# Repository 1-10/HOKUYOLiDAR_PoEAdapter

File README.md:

# HOKUYO LiDAR PoEAdapter

## はじめに

 HOKUYO LiDAR(USTシリーズ)のPoE化に関する資料です。
 
## フォルダ構成
| フォルダ名 | 内容 |
|:---------|:-----|
| App | 動作確認用App Installer |
| Eagle | Eagle回路図 |
| Pic | 画像 |
| stl | 基板ケースSTL |

## 動作確認用App
動作確認用Appは以下を利用しています。WindowsOSのみ対応。
* [URG Benri Lite](https://urgbenri.sourceforge.net/jp/)
## ドキュメント
* [1-10LabBlog](Link)
  * 基板発注先によってデザインルールが異なるため、ガーバーデータは含まれていません。
  * 3Dプリンタ機器によってデータ拡張子が異なるため、STLデータのみになります。

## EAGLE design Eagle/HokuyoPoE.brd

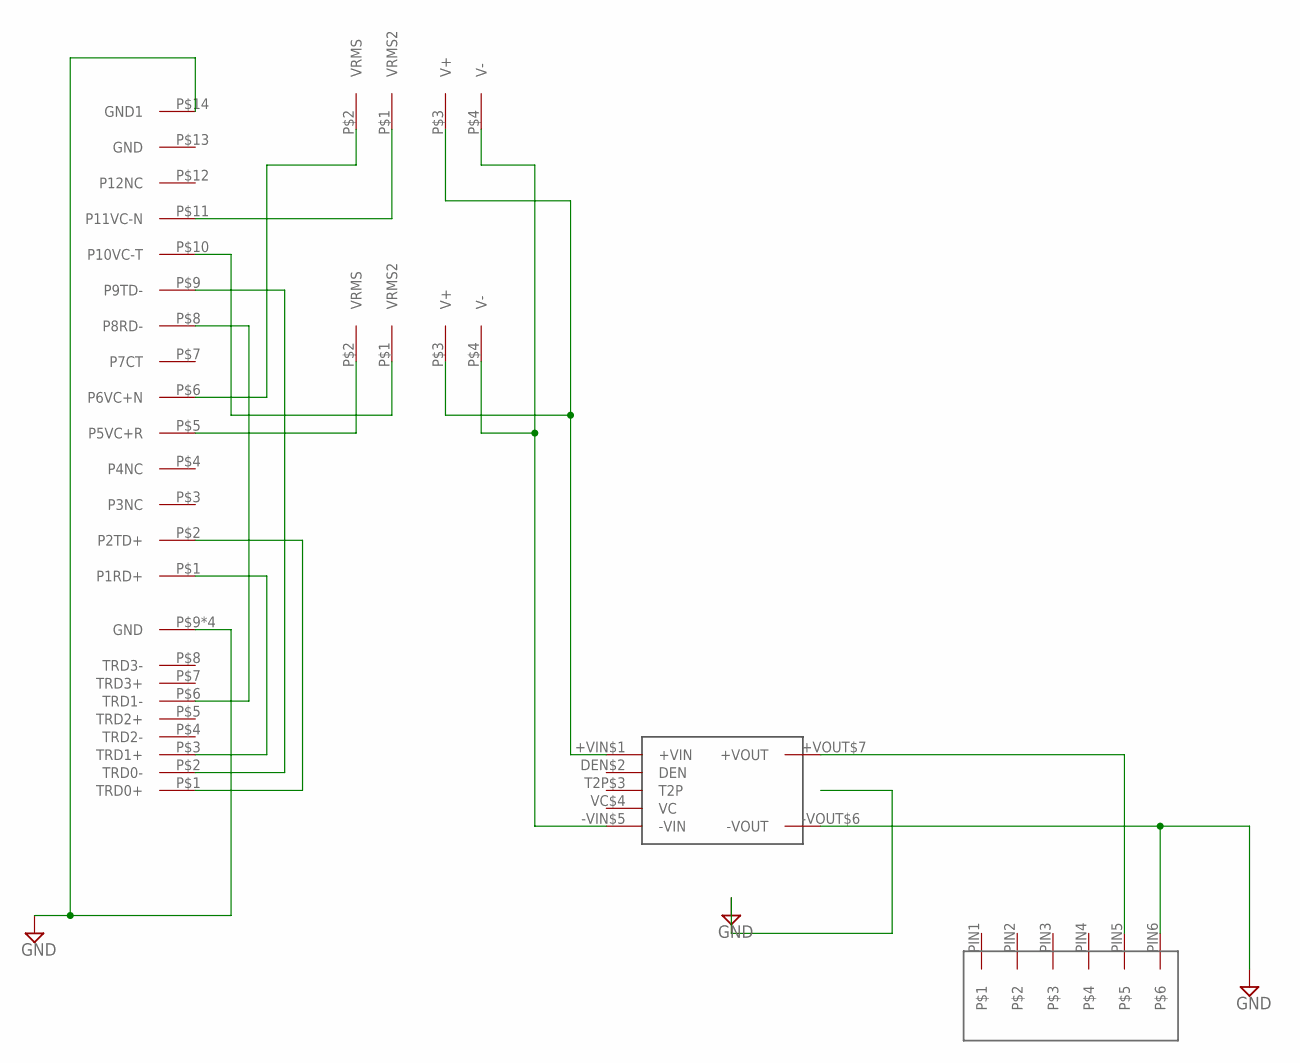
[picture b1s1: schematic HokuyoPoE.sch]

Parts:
U$1: MYBSP0122BABFT
U$2: 7810-XPXC[RJ45]
U$3, U$6: B1010S
U$4: SM08B-SRSS-TB
U$5: 0813-1X1T-57-F

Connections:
GND: U$1.-VOUT$6 (-VOUT), U$2.P$9 (GND), U$2.P$10 (GND), U$2.P$11 (GND), U$2.P$12 (GND), U$4.PIN6, U$5.P$14 (GND1)
unnamed: U$2.P$3 (TRD1+), U$5.P$1 (P1RD+)
unnamed: U$5.P$10 (P10VC-T), U$6.P$1 (VRMS2)
unnamed: U$5.P$5 (P5VC+R), U$6.P$2 (VRMS)
unnamed: U$3.P$1 (VRMS2), U$5.P$11 (P11VC-N)
unnamed: U$3.P$2 (VRMS), U$5.P$6 (P6VC+N)
unnamed: U$1.+VIN$1 (+VIN), U$3.P$3 (V+), U$6.P$3 (V+)
unnamed: U$2.P$6 (TRD1-), U$5.P$8 (P8RD-)
unnamed: U$1.-VIN$5 (-VIN), U$3.P$4 (V-), U$6.P$4 (V-)
unnamed: U$2.P$1 (TRD0+), U$5.P$2 (P2TD+)
unnamed: U$2.P$2 (TRD0-), U$5.P$9 (P9TD-)
unnamed: U$1.+VOUT$7 (+VOUT), U$4.PIN5

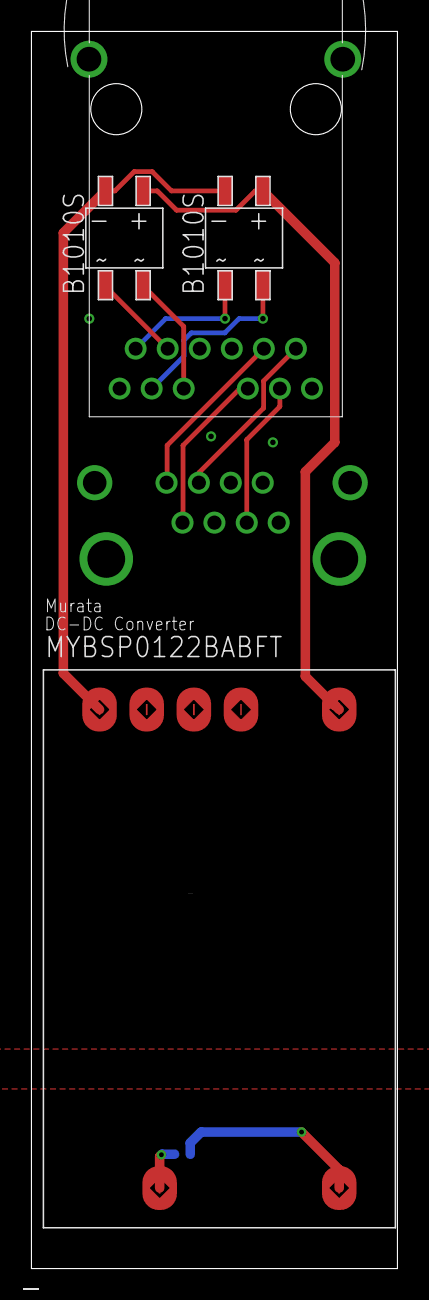
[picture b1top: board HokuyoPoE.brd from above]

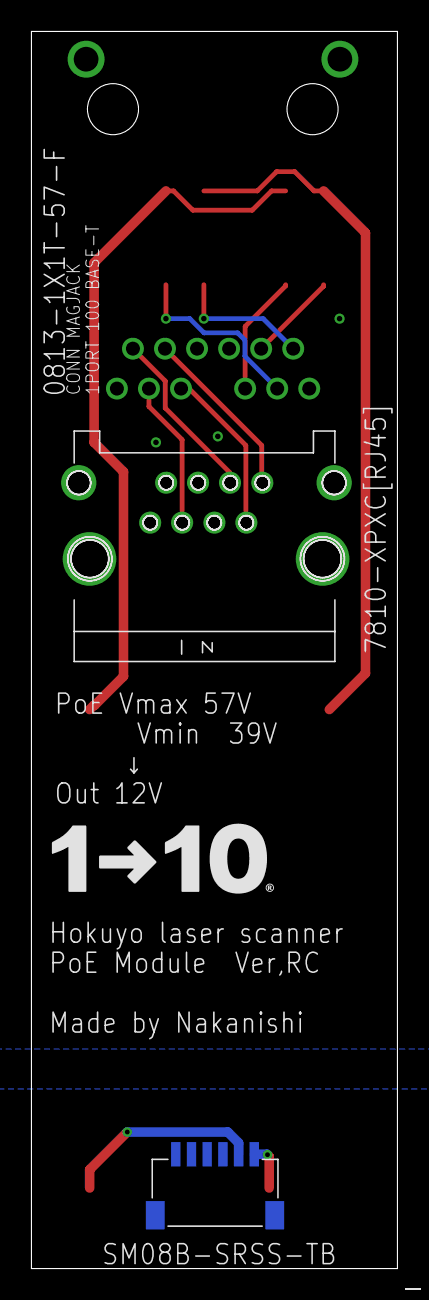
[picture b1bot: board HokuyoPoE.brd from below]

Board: 2 copper layers, 23.3 x 78.7 mm, 6 parts (3 on the bottom side), 12 nets.

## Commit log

2023-07-19 Update README.md
    Add md template
2023-07-19 Add Pic folder
2023-07-19 Add EagleData Pic
2023-07-19 Add Eagle folder
2023-07-19 Add stl folder
2023-07-19 Add App folder
